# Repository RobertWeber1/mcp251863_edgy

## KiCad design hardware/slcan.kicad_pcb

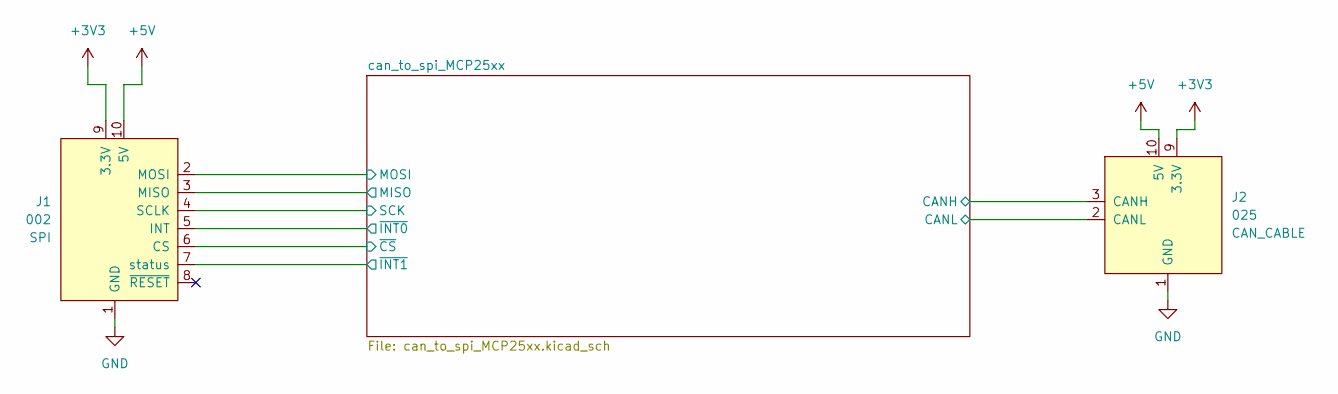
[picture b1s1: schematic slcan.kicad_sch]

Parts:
J1: 002; on_edge_2x05_device
J2: 025; on_edge_2x05_host

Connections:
+3V3: J1.9 (3.3V), J2.9 (3.3V); also elsewhere on the board
+5V: J1.10 (5V), J2.10 (5V); also elsewhere on the board
/can_to_spi_MCP25xx/CANH: J2.3 (CANH); also elsewhere on the board
/can_to_spi_MCP25xx/CANL: J2.2 (CANL); also elsewhere on the board
/can_to_spi_MCP25xx/MISO: J1.3 (MISO); also elsewhere on the board
/can_to_spi_MCP25xx/MOSI: J1.2 (MOSI); also elsewhere on the board
/can_to_spi_MCP25xx/SCK: J1.4 (SCLK); also elsewhere on the board
/can_to_spi_MCP25xx/~CS: J1.6 (CS); also elsewhere on the board
/can_to_spi_MCP25xx/~INT0: J1.5 (INT); also elsewhere on the board
/can_to_spi_MCP25xx/~INT1: J1.7 (status); also elsewhere on the board
GND: J1.1 (GND), J2.1 (GND); also elsewhere on the board

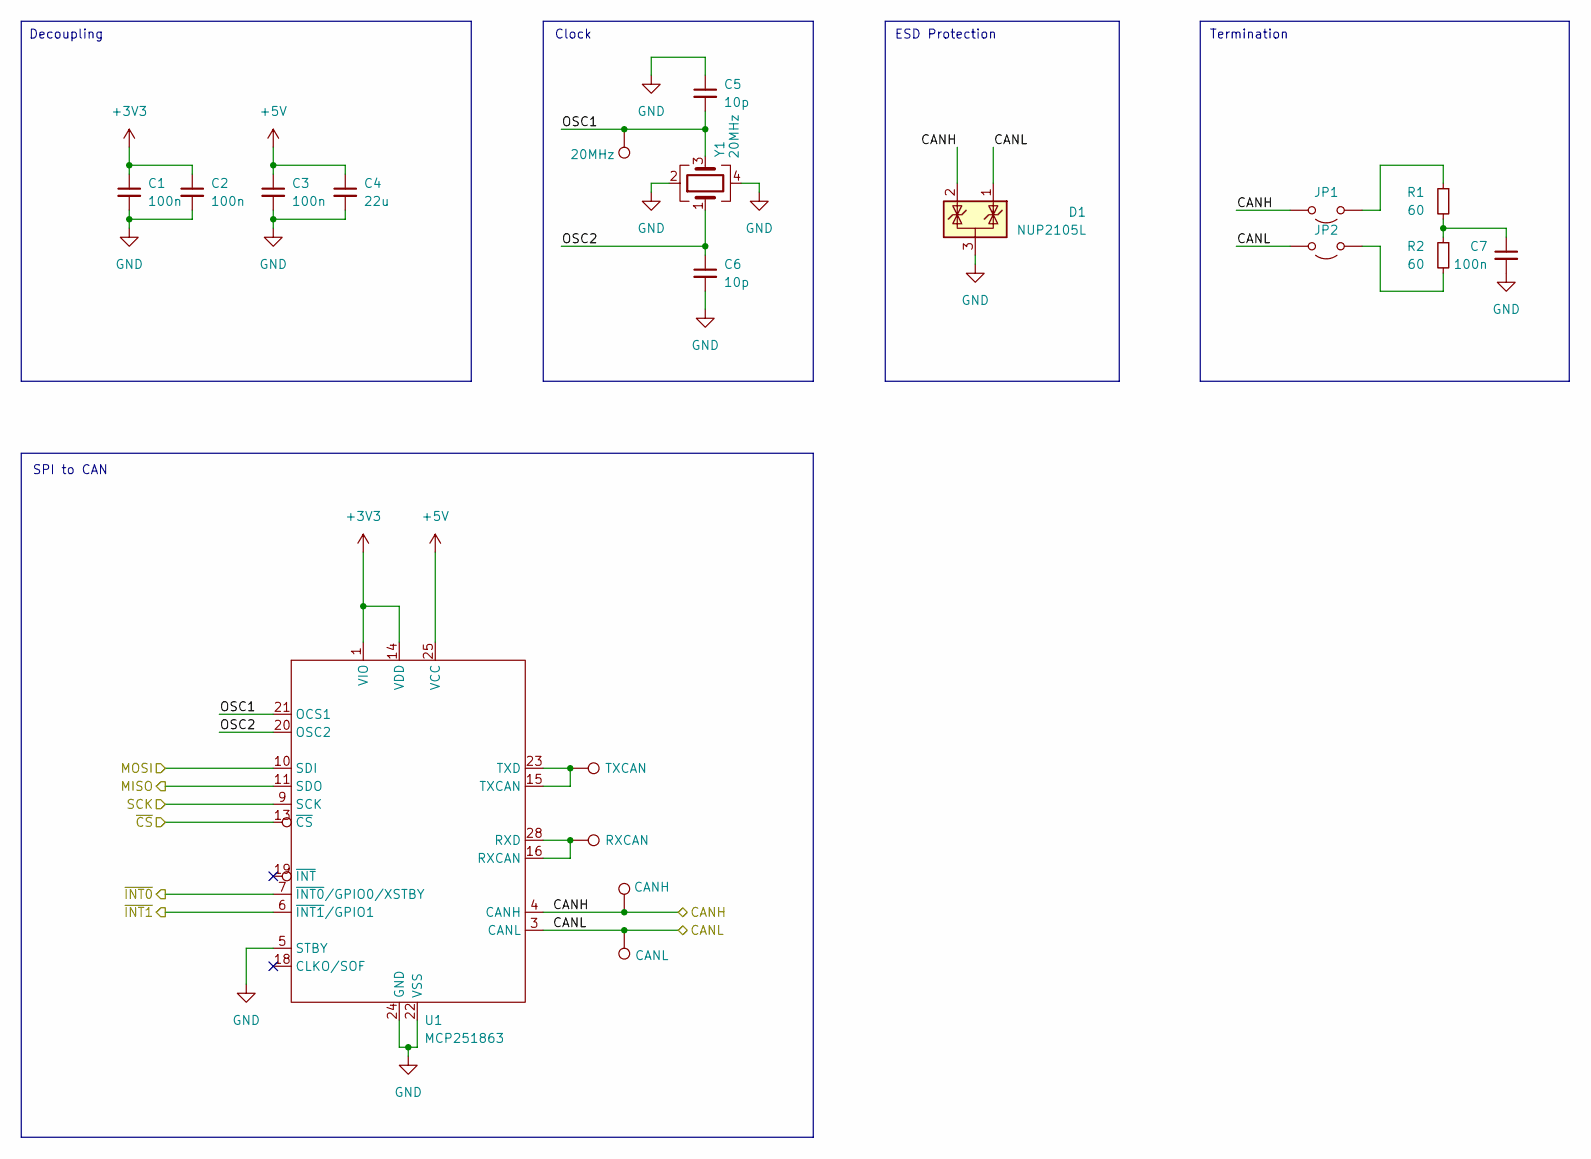
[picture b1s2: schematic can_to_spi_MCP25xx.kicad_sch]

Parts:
C1, C2, C3, C7: 100n; C_0402_1005Metric; LCSC Part# C1525
C4: 22u; C_0402_1005Metric; LCSC Part# C22367823
C5, C6: 10p; C_0402_1005Metric; LCSC Part# C32949
D1: NUP2105L; SOT-23; LCSC Part# C5158054
JP1, JP2: Jumper_2_Open; PinHeader_1x02_P2.54mm_Vertical
R1, R2: 60; R_0603_1608Metric; LCSC Part# C203704
TP1: TXCAN; TestPoint_THTPad_D1.0mm_Drill0.5mm
TP2: RXCAN; TestPoint_THTPad_D1.0mm_Drill0.5mm
TP3: CANH; TestPoint_THTPad_D1.0mm_Drill0.5mm
TP4: CANL; TestPoint_THTPad_D1.0mm_Drill0.5mm
TP5: 20MHz; TestPoint_THTPad_D1.0mm_Drill0.5mm
U1: MCP251863; SSOP-28_5.3x10.2mm_P0.65mm; LCSC Part# C5226885
Y1: 20MHz; Crystal_SMD_3225-4Pin_3.2x2.5mm; LCSC Part# C7275100

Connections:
+3V3: C1.1, C2.1, U1.1 (VIO), U1.14 (VDD); also elsewhere on the board
+5V: C3.1, C4.1, U1.25 (VCC); also elsewhere on the board
/can_to_spi_MCP25xx/CANH: D1.2 (K), JP1.2 (B), TP3.1, U1.4 (CANH); also elsewhere on the board
/can_to_spi_MCP25xx/CANL: D1.1 (K), JP2.2 (B), TP4.1, U1.3 (CANL); also elsewhere on the board
/can_to_spi_MCP25xx/MISO: U1.11 (SDO); also elsewhere on the board
/can_to_spi_MCP25xx/MOSI: U1.10 (SDI); also elsewhere on the board
/can_to_spi_MCP25xx/OSC1: C5.2, TP5.1, U1.21 (OCS1), Y1.3
/can_to_spi_MCP25xx/OSC2: C6.1, U1.20 (OSC2), Y1.1
/can_to_spi_MCP25xx/SCK: U1.9 (SCK); also elsewhere on the board
/can_to_spi_MCP25xx/~CS: U1.13 (~CS); also elsewhere on the board
/can_to_spi_MCP25xx/~INT0: U1.7 (~INT0/GPIO0/XSTBY); also elsewhere on the board
/can_to_spi_MCP25xx/~INT1: U1.6 (~INT1/GPIO1); also elsewhere on the board
GND: C1.2, C2.2, C3.2, C4.2, C5.1, C6.2, C7.2, D1.3 (A), U1.5 (STBY), U1.22 (VSS), U1.24 (GND), Y1.2, Y1.4; also elsewhere on the board
unnamed: C7.1, R1.2, R2.1
unnamed: JP1.1 (A), R1.1
unnamed: JP2.1 (A), R2.2
unnamed: TP2.1, U1.16 (RXCAN), U1.28 (RXD)
unnamed: TP1.1, U1.15 (TXCAN), U1.23 (TXD)

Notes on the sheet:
Clock
ESD Protection
Termination
SPI to CAN
Decoupling

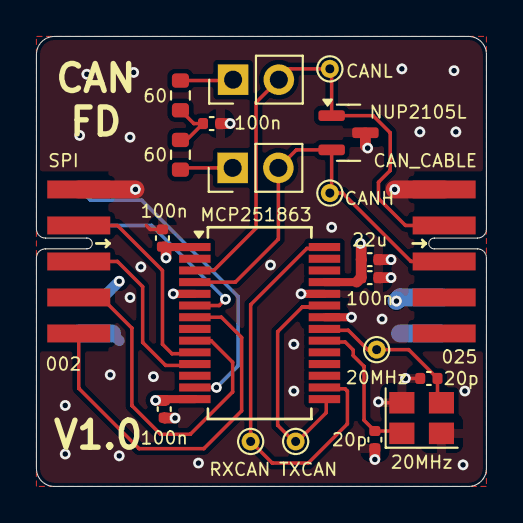
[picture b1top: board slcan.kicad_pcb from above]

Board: 4 copper layers, 25.0 x 25.0 mm, 21 parts (0 on the bottom side), 18 nets.

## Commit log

2024-10-13 Add put_on_edge as submodule
2024-10-13 Refactor hardware dir
2024-10-25 V1.0
